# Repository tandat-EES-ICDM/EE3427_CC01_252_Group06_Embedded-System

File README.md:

[Demo Video]:  
https://drive.google.com/file/d/16Uh21a4lqSv_YghYvDpnQTZxxrZzBnIu/view?usp=drive_link  
[Demo Video - Revised: Add 2 more non-volatile alarms -> total 3 alarms]:  
https://drive.google.com/file/d/1G-kM-oG9oD7Pn4vBYBXZ9WEiFOjN3P8L/view?usp=sharing

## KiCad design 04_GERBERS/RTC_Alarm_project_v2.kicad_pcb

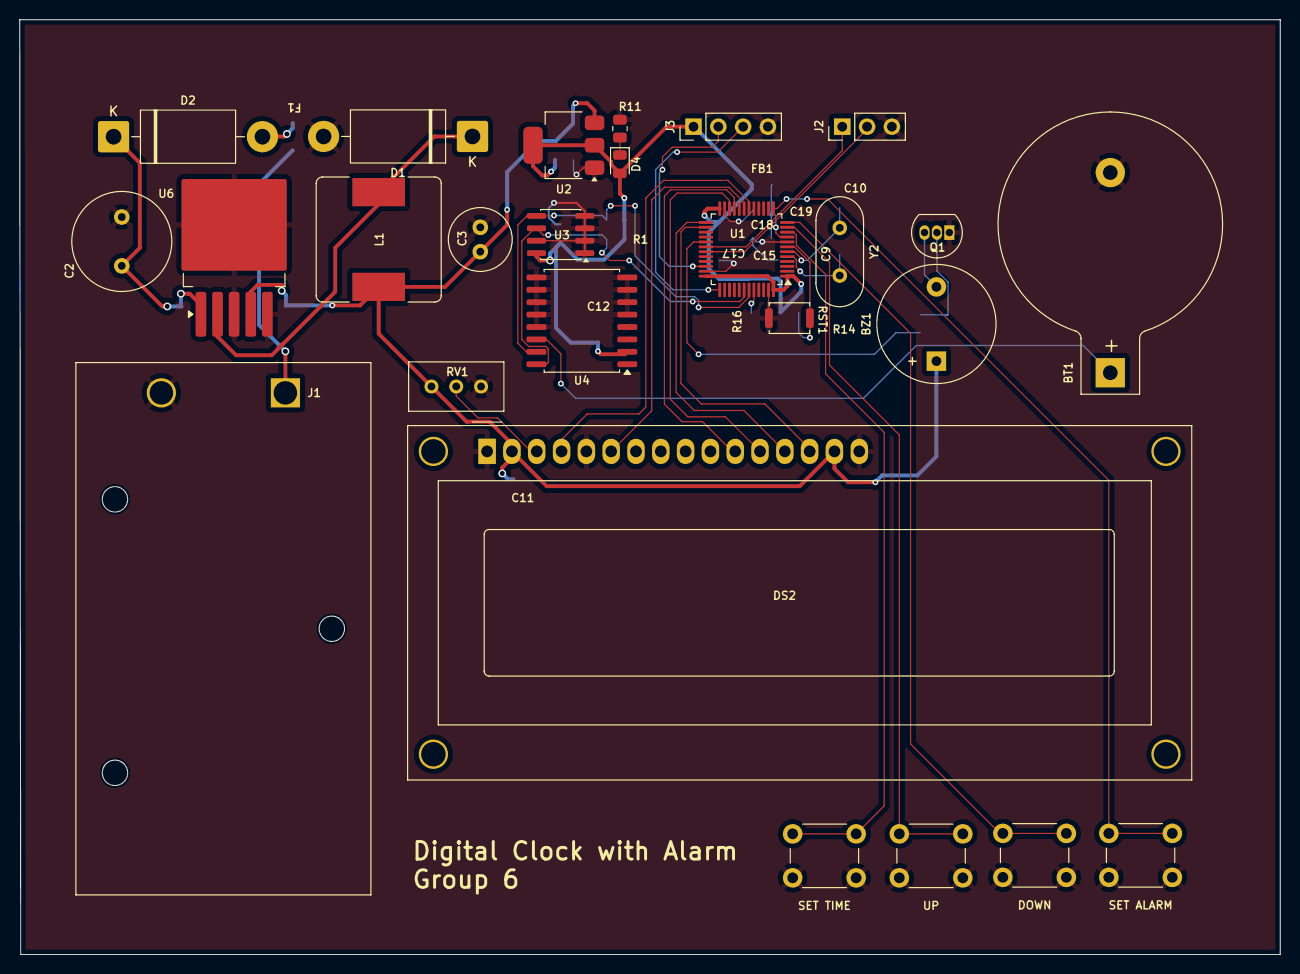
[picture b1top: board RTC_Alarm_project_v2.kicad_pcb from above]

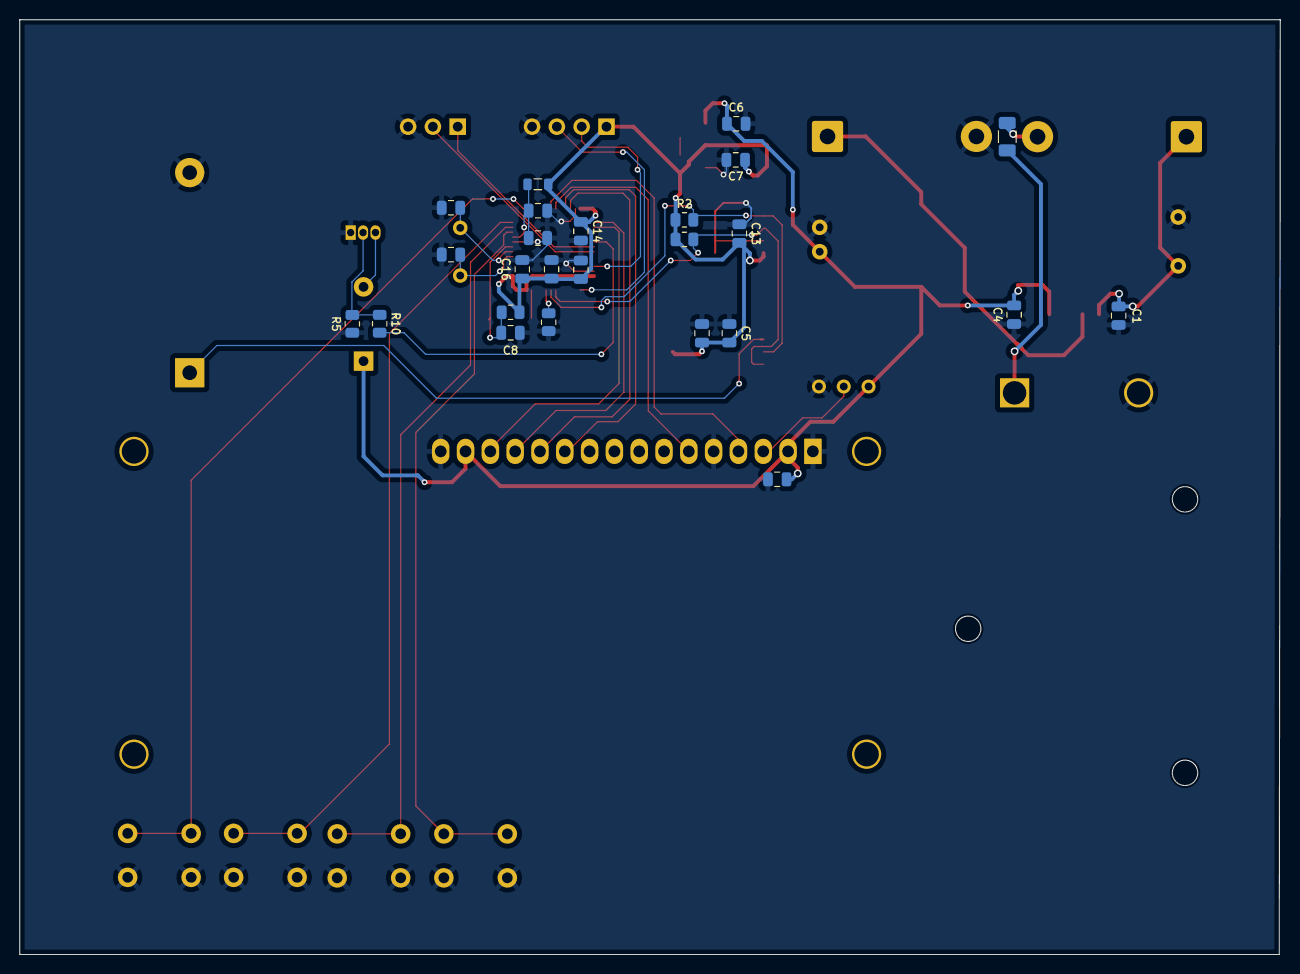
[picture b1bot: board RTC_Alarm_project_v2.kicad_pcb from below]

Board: 4 copper layers, 129.1 x 95.7 mm, 51 parts (25 on the bottom side), 34 nets.

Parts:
BT1: Battery_Cell; BatteryHolder_Keystone_103_1x20mm
BZ1: Buzzer; Buzzer_12x9.5RM7.6
C1, C4, C5, C8, C11, C12, C13, C14, C15, C16, C17, C18, C19: 100nF; C_0805_2012Metric
C2: 680uF; C_Radial_D10.0mm_H16.0mm_P5.00mm
C3: 220uF; C_Radial_D6.3mm_H7.0mm_P2.50mm
C6, C7: 22uF; C_0805_2012Metric
C9, C10: 22pF; C_0805_2012Metric
D1, D2: 1N5822; D_DO-201AD_P15.24mm_Horizontal
D4: LED; LED_0805_2012Metric
DOWN: SW_Push; SW_PUSH_6mm
DS2: WC1602A
F1: Polyfuse_Small; Fuse_1206_3216Metric
FB1: 120 Ohm 100MHz; L_0805_2012Metric
J1: Conn_01x02_Socket; BatteryHolder_Eagle_12BH611-GR
J2: Conn_01x03_Pin; PinHeader_1x03_P2.54mm_Vertical
J3: Conn_01x04_Pin; PinHeader_1x04_P2.54mm_Vertical
L1: 33uH; L_Bourns_SRR1260
Q1: S8050; TO-92_Inline
R1, R2: 4.7k; R_0805_2012Metric
R5, R14, R16: 10k; R_0805_2012Metric
R10, R11: 1k; R_0805_2012Metric
RST1: SW_Push; SW_Push_SPST_NO_Alps_SKRK
RV1: 10k; Potentiometer_Bourns_3296W_Vertical
SET ALARM: SW_Push; SW_PUSH_6mm
SET TIME: SW_Push; SW_PUSH_6mm
U1: STM32F103C8Tx; LQFP-48_7x7mm_P0.5mm
U2: AMS1117-3.3; SOT-223-3_TabPin2
U3: AT24CS32-SSHM; SOIC-8_3.9x4.9mm_P1.27mm
U4: DS3231M; SOIC-16W_7.5x10.3mm_P1.27mm
U6: LM2596S-5; TO-263-5_TabPin3
UP: SW_Push; SW_PUSH_6mm
Y2: 8MHz; Crystal_HC49-4H_Vertical

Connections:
+3.3V: C5.2, C7.1, C12.2, C13.2, C14.1, C15.1, C16.1, C17.1, D4.2 (A), FB1.1, J3.1, R1.1, R2.1, R14.1, U1.1 (VBAT), U1.24 (VDD), U1.36 (VDD), U1.48 (VDD), U2.2 (VO), U3.8 (VCC), U4.2 (VCC)
+5V: BZ1.1 (+), C3.1, C4.2, C6.1, C11.2, DS2.2 (VDD), DS2.15 (LED(+)), L1.2, RV1.3, U2.3 (VI), U6.4 (FB)
/main_schematic/BUZZER: R10.2, U1.29 (PA8)
/main_schematic/D4: DS2.11 (D4), U1.21 (PB10)
/main_schematic/D5: DS2.12 (D5), U1.22 (PB11)
/main_schematic/D6: DS2.13 (D6), U1.25 (PB12)
/main_schematic/D7: DS2.14 (D7), U1.26 (PB13)
/main_schematic/DOWN: DOWN.2, U1.12 (PA2)
/main_schematic/E: DS2.6 (E), U1.19 (PB1)
/main_schematic/OSC_IN: C9.2, U1.5 (PD0), Y2.2
/main_schematic/OSC_OUT: C10.2, U1.6 (PD1), Y2.1
/main_schematic/RESET: C8.1, R14.2, RST1.2, U1.7 (NRST)
/main_schematic/RS: DS2.4 (RS), U1.18 (PB0)
/main_schematic/RXD: J2.2, U1.31 (PA10)
/main_schematic/SCL: R1.2, U1.42 (PB6), U3.6 (SCL), U4.16 (SCL)
/main_schematic/SDA: R2.2, U1.43 (PB7), U3.5 (SDA), U4.15 (SDA)
/main_schematic/SET_ALARM: SET ALARM.2, U1.13 (PA3)
/main_schematic/SET_TIME: SET TIME.2, U1.10 (PA0)
/main_schematic/SWCLK: J3.3, U1.37 (PA14)
/main_schematic/SWDIO: J3.2, U1.34 (PA13)
/main_schematic/TXD: J2.1, U1.30 (PA9)
/main_schematic/UP: U1.11 (PA1), UP.2
GND: BT1.2 (-), C1.1, C2.2, C3.2, C4.1, C5.1, C6.2, C7.2, C8.2, C9.1, C10.1, C11.1, C12.1, C13.1, C14.2, C15.2, C16.2, C17.2, C18.2, C19.2, D1.2 (A), DOWN.1, DS2.1 (VSS), DS2.5 (R/W), DS2.16 (LED(-)), J1.2, J2.3, J3.4, Q1.1 (E), R5.1, R11.2, R16.1, RST1.1, RV1.1, SET ALARM.1, SET TIME.1, U1.8 (VSSA), U1.23 (VSS), U1.35 (VSS), U1.47 (VSS), U2.1 (GND), U3.1 (A0), U3.2 (A1), U3.3 (A2), U3.4 (GND), U3.7 (WP), U4.5 (GND), U4.6 (GND), U4.7 (GND), U4.8 (GND), U4.9 (GND), U4.10 (GND), U4.11 (GND), U4.12 (GND), U4.13 (GND), U6.3 (GND), U6.5 (~ON/OFF), UP.1
unnamed: BT1.1 (+), U4.14 (VBAT)
unnamed: BZ1.2 (-), Q1.3 (C)
unnamed: D1.1 (K), L1.1, U6.2 (OUT)
unnamed: D2.2 (A), F1.1
unnamed: C1.2, C2.1, D2.1 (K), U6.1 (VIN)
unnamed: D4.1 (K), R11.1
unnamed: DS2.3 (VO), RV1.2
unnamed: F1.2, J1.1
unnamed: Q1.2 (B), R5.2, R10.1
unnamed: R16.2, U1.44 (BOOT0)
unnamed: C18.1, C19.1, FB1.2, U1.9 (VDDA)

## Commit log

2026-01-25 Create Functional-Requirement
    Functional Requirement
2026-01-25 Non Functional Requirement by tdat
2026-03-09 Create 01_DESIGN
2026-03-09 Create test
2026-03-09 Rename Bill of Materials.xlsx to 03_BOM/Bill of Materials.xlsx
2026-03-09 Rename Requirements.xlsx to 01_DESIGN/Requirements.xlsx
2026-03-09 Rename Schematic (Kicad).pdf to 02_Schematic_pdf/Schematic (Kicad).pdf
2026-03-09 Upload Requirement Ver2
2026-03-30 Add demo video link to README
2026-05-07 Update demo video links in README
    Added a revised demo video link and updated the original link format.
2026-05-11 Create Firmware
